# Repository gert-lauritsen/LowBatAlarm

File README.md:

# LowBatAlarm

## Beskrivelse
Simple alarm for low bat. Baseret på en lille coparator, med en 0.6V indbygget ref. Der er monteret en 33V zener til at beskytte 
mod overspænding fra induktiv indkobling. Udgangen er en 8A 60V fet, men der er sat en serie modstand i, således at strømmer aldrig bliver for stor.
Der sidder en 40V LDO til at lave 3.3V. Hvis spændingen er over Vcut, vil en lille grøn lampe lyse.

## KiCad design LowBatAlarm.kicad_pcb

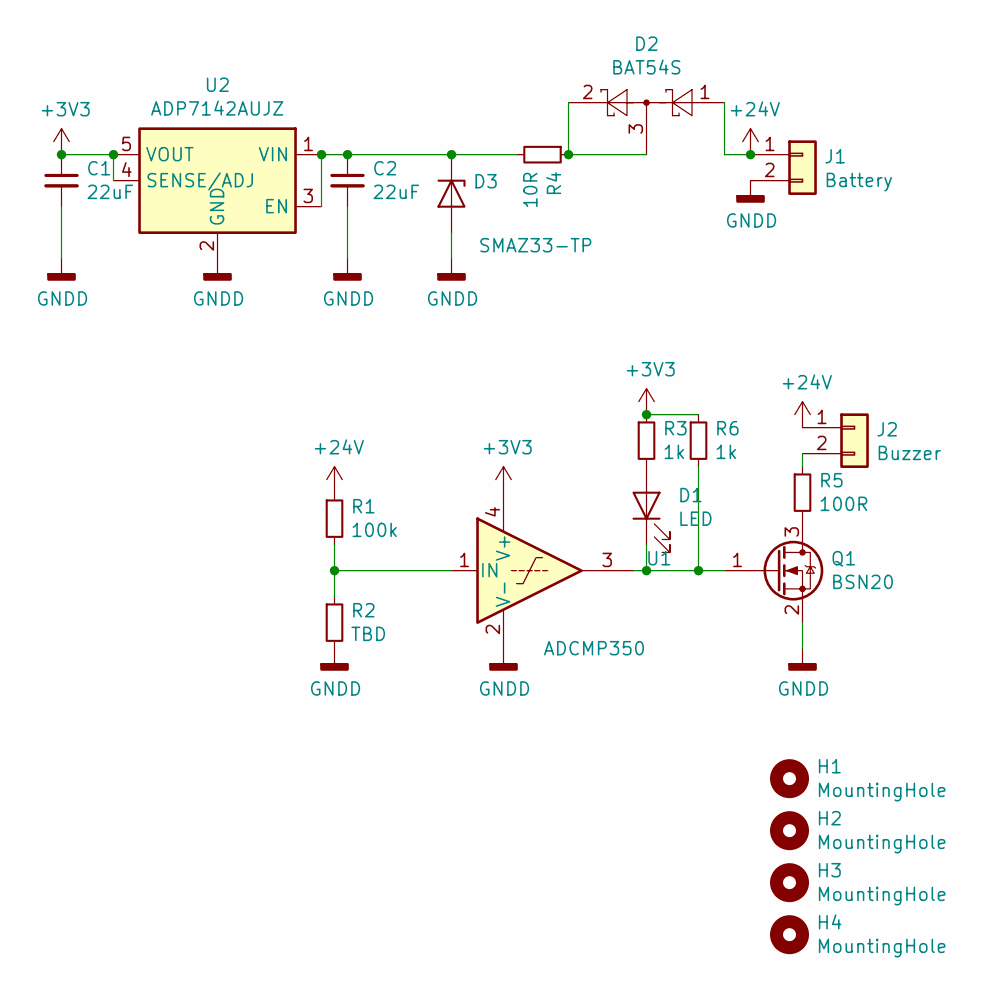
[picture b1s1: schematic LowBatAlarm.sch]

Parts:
C1, C2: 22uF; C_0805_2012Metric
D1: LED; LED_0805_2012Metric
D2: BAT54S; SOT-23
D3: SMAZ33-TP; D_SMA
H1, H2, H3, H4: MountingHole; MountingHole_3.2mm_M3
J1: Battery; Molex_KK-254_AE-6410-02A_1x02_P2.54mm_Vertical
J2: Buzzer; Molex_KK-254_AE-6410-02A_1x02_P2.54mm_Vertical
Q1: BSN20; SOT-23
R1: 100k; R_0805_2012Metric
R2: TBD; R_0805_2012Metric
R3, R6: 1k; R_0805_2012Metric
R4: 10R; R_0805_2012Metric
R5: 100R; R_0805_2012Metric
U1: ADCMP350; Analog_KS-4
U2: ADP7142AUJZ; TSOT-23-5

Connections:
+3V3: C1.1, R3.1, R6.1, U1.4 (V+), U2.4 (SENSE/ADJ), U2.5 (VOUT)
+24V: D2.1, J1.1, J2.1, R1.1
GNDD: C1.2, C2.2, D3.2 (A), J1.2, Q1.2 (S), R2.2, U1.2 (V-), U2.2 (GND)
unnamed: C2.1, D3.1 (K), R4.2, U2.1 (VIN), U2.3 (EN)
unnamed: D1.1 (K), Q1.1 (G), R6.2, U1.3
unnamed: D1.2 (A), R3.2
unnamed: D2.2, D2.3, R4.1
unnamed: J2.2, R5.1
unnamed: Q1.3 (D), R5.2
unnamed: R1.2, R2.1, U1.1 (IN)

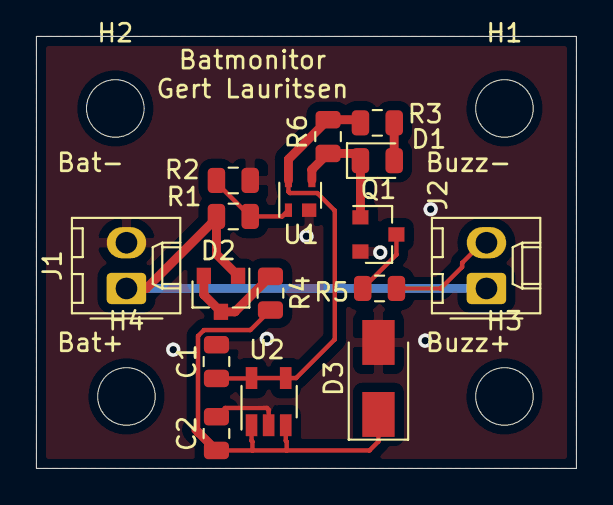
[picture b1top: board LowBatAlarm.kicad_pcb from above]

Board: 2 copper layers, 30.0 x 24.0 mm, 20 parts (0 on the bottom side), 10 nets.

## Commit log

2020-06-10 init
    Init
2020-06-10 Add pdf
2020-06-16 Ny beregning
2020-06-17 PCB opdatering
